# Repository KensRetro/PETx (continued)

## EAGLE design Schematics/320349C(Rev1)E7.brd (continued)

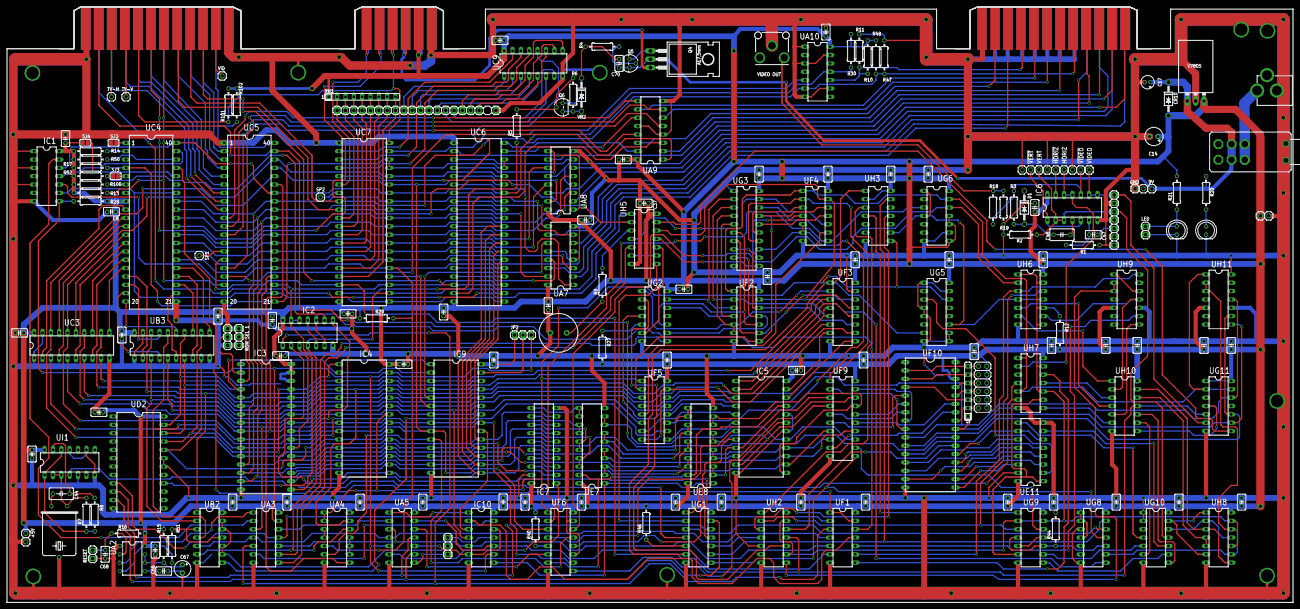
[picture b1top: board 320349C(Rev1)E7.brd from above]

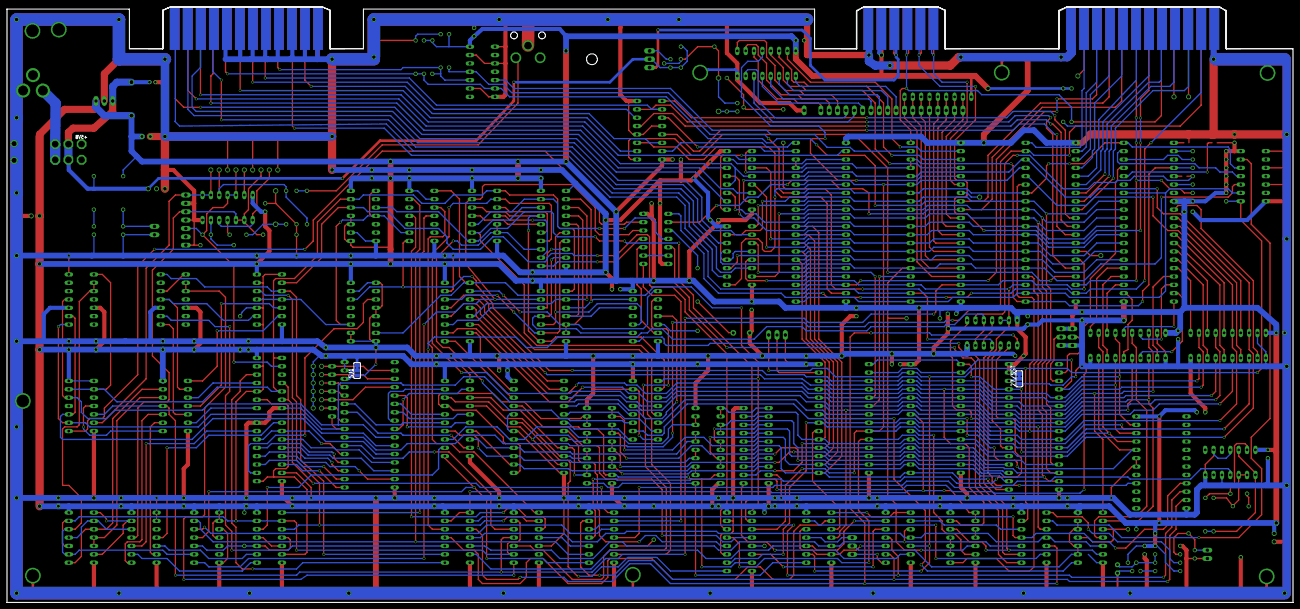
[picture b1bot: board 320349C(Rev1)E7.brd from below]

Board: 2 copper layers, 390.9 x 181.0 mm, 211 parts (2 on the bottom side), 331 nets.

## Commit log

2024-05-08 Create Folder
